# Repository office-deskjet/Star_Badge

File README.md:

## Star Badge
Inspired from Super Mario Brothers Super Star.  

### Features
5 SAO 1.69bis connectors, suporting I2C, X2 and X5 support GPIO.
Power by 2x AA batteries or USB micro
3.3 Volts, 1.5 Amps regulated

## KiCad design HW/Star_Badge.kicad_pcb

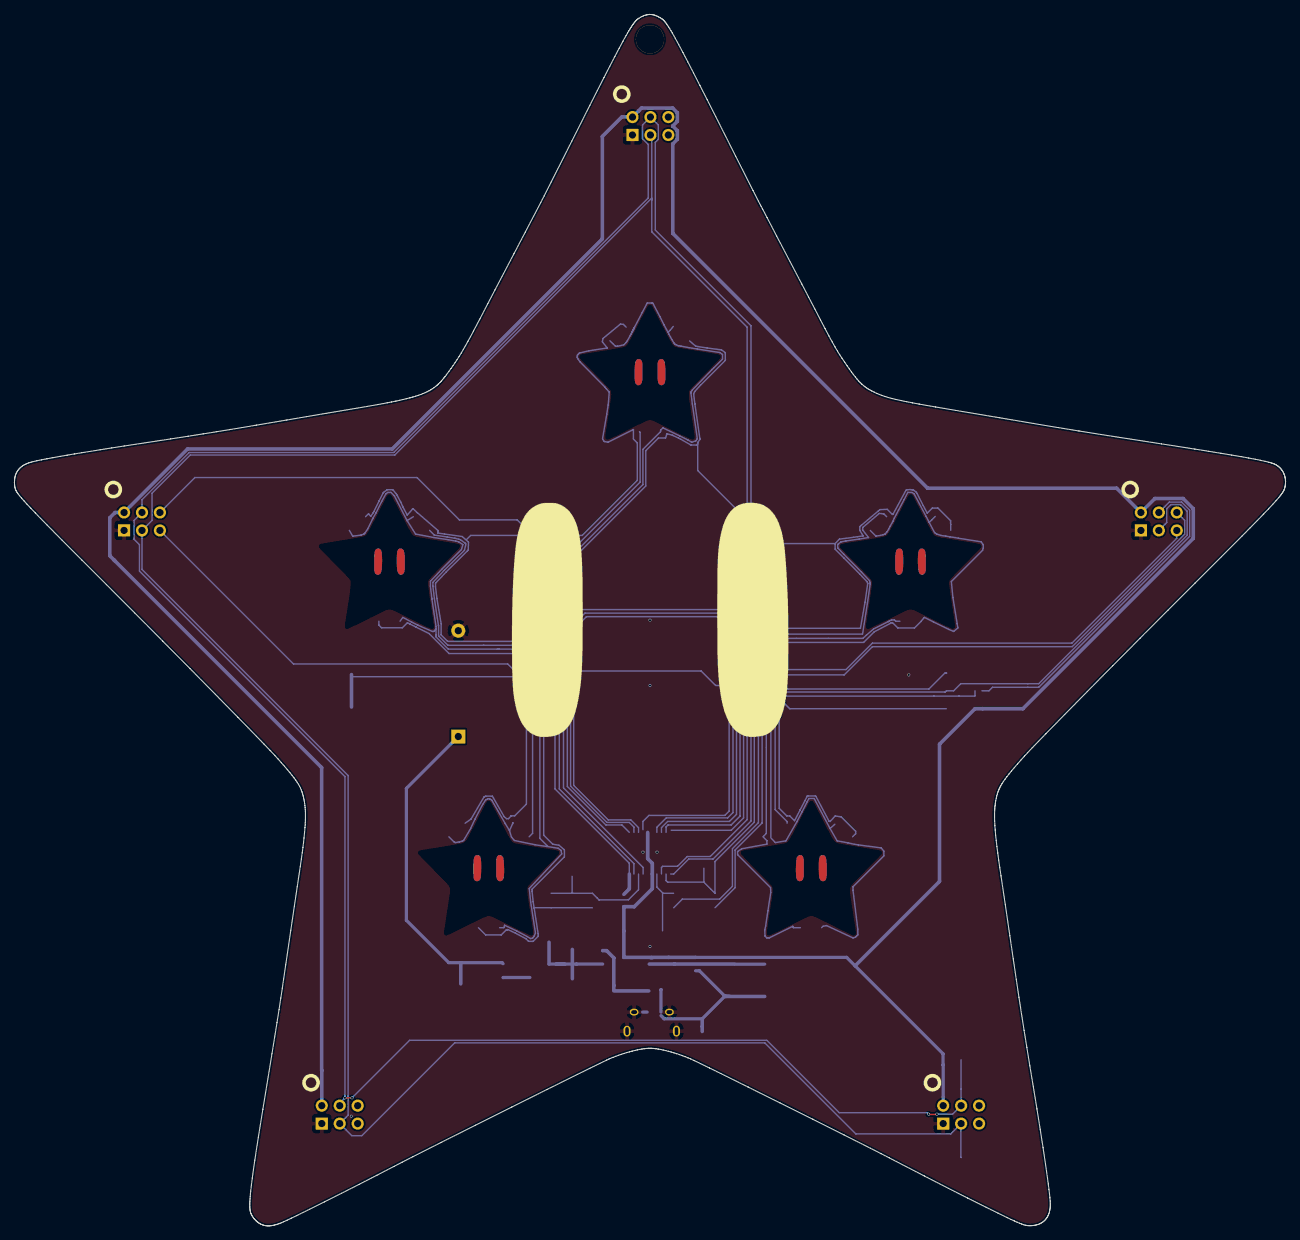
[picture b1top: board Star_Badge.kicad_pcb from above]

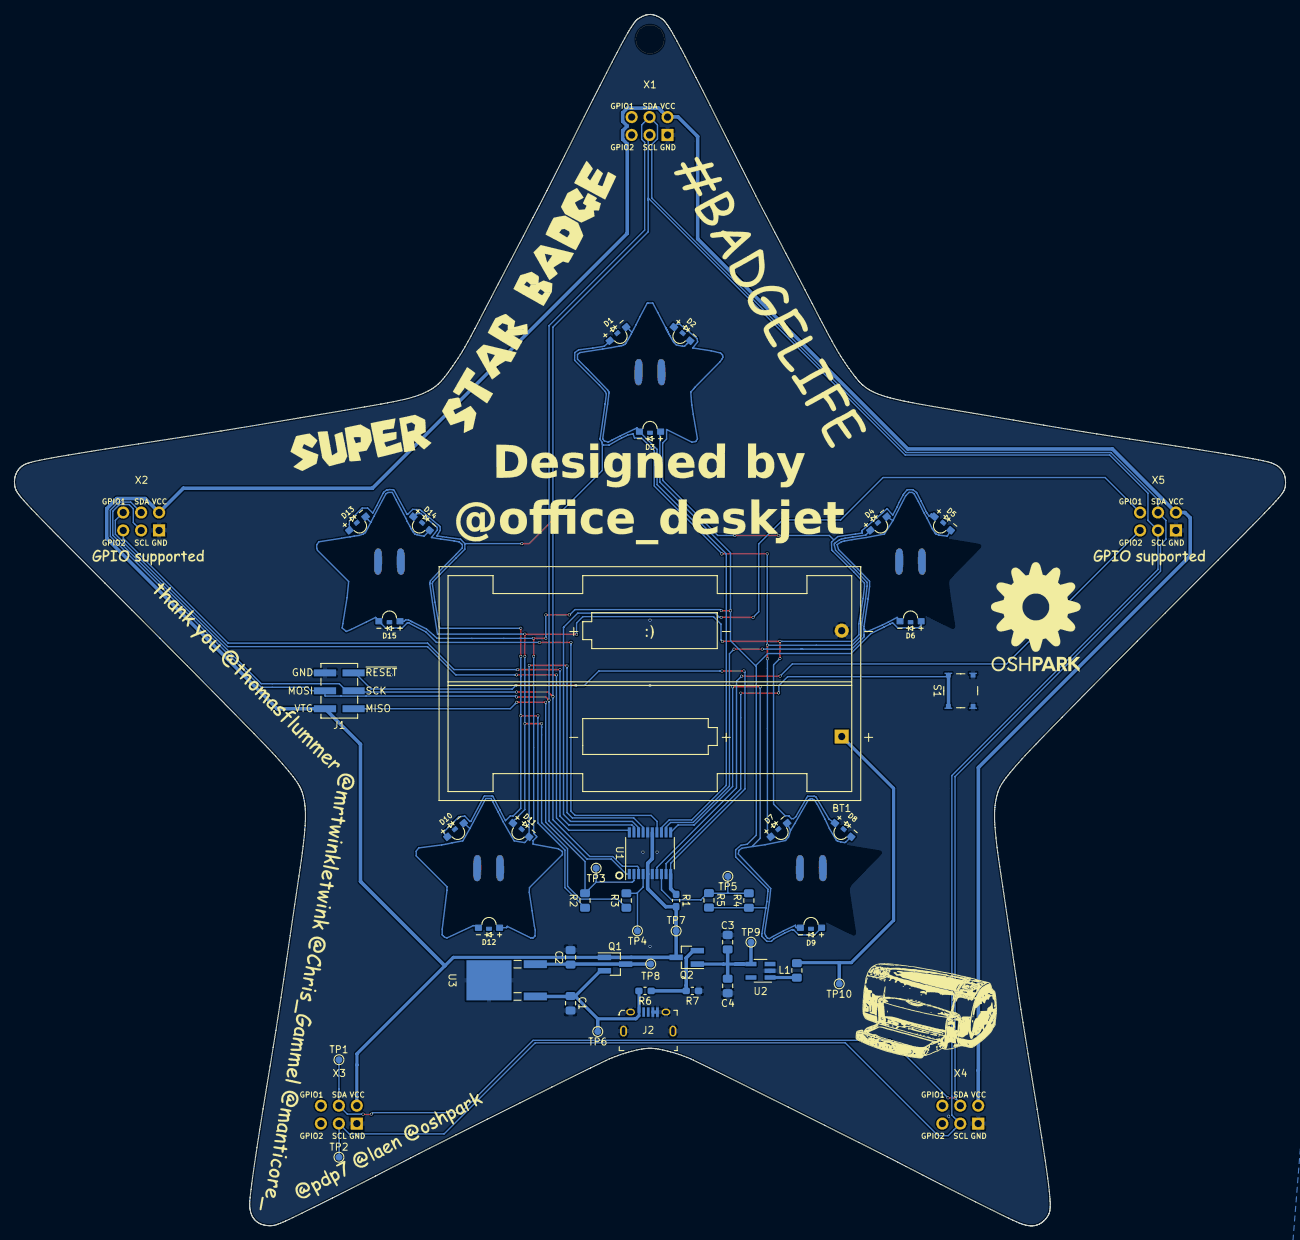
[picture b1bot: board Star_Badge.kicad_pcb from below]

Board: 2 copper layers, 180.0 x 171.6 mm, 51 parts (46 on the bottom side), 27 nets.

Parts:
BT1: Battery; BatteryHolder_Keystone_2462_2xAA
C1, C2, C3, C4: 10uF; C_0805_2012Metric_Pad1.15x1.40mm_HandSolder
D1, D4, D7, D10, D13: R_LED; 1204_SIDE_VIEW_LED
D2, D5, D8, D11, D14: G_LED; 1204_SIDE_VIEW_LED
D3, D6, D9, D12, D15: B_LED; 1204_SIDE_VIEW_LED
J1: AVR-ISP-6; AVR_ISP_2x3_P2.54mm_SMD
J2: 10118194-0001LF; USB_Micro_B_Female_10118194-0001LF
L1: 4.7uH; L_0805_2012Metric_Pad1.15x1.40mm_HandSolder
Q1: Q_NMOS_DGS; SOT-23_Handsoldering
Q2: Q_PMOS_DGS; SOT-23_Handsoldering
R1, R7: 6K8; R_0603_1608Metric_Pad1.05x0.95mm_HandSolder
R2, R4, R5: 50R; R_0805_2012Metric_Pad1.15x1.40mm_HandSolder
R3: 100R; R_0805_2012Metric_Pad1.15x1.40mm_HandSolder
R6: 4K7; R_0603_1608Metric_Pad1.05x0.95mm_HandSolder
S1: TL3315NF160Q; Switch_Tactile_SMD_4.5x4.5mm_TL3315NF160Q
TP1, TP2, TP3, TP4, TP5, TP6, TP7, TP8, TP9, TP10: TestPoint; TestPoint_Pad_D1.0mm
U1: ATTINY861-15XD; TSSOP-20_4.4x6.5mm_P0.65mm
U2: TPS613221ADBVT; SOT-23-5_HandSoldering
U3: AP7363-33D-13
X1, X2, X3, X4, X5: Badgelife_sao_connector_v169bis; Badgelife-SAOv169-BADGE-2x3

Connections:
/B_LED_BUS: D3.2, D6.2, D9.2, D12.2, D15.2, R4.1, R5.1
/B_PWM: R4.2, R5.2, TP5.1, U1.8
/Button: S1.1, S1.2, U1.9
/EN_RGB0: D10.1, D11.1, D12.1, U1.17
/EN_RGB1: D13.1, D14.1, D15.1, U1.14
/EN_RGB2: D1.1, D2.1, D3.1, U1.13
/EN_RGB3: D4.1, D5.1, D6.1, U1.12
/EN_RGB4: D7.1, D8.1, D9.1, U1.11
/GPIO_1_1: U1.20, X2.5
/GPIO_1_2: U1.19, X2.6
/GPIO_2_1: U1.18, X5.5
/GPIO_2_2: U1.7, X5.6
/G_LED_BUS: D2.2, D5.2, D8.2, D11.2, D14.2, R3.1
/G_PWM: R3.2, TP4.1, U1.4
/R_LED_BUS: D1.2, D4.2, D7.2, D10.2, D13.2, R2.1
/R_PWM__MISO: J1.1, R2.2, TP3.1, U1.2
/SCL_SCK: J1.3, TP2.1, U1.3, X1.4, X2.4, X3.4, X4.4, X5.4
/SDA_MOSI: J1.4, TP1.1, U1.1, X1.3, X2.3, X3.3, X4.3, X5.3
/VBUS: J1.2, Q1.1, Q2.3, R1.2, TP7.1, U1.5, U1.15, X1.1, X2.1, X3.1, X4.1, X5.1
/V_BAT: C3.1, C4.1, Q2.1, TP9.1, U2.4
/V_REG: C2.1, Q1.3, TP8.1, U3.3
/V_USB: C1.1, J2.1, Q1.2, R6.2, TP6.1, U3.1
/~RESET: J1.5, R1.1, U1.10
GND: BT1.2, C1.2, C2.2, C3.2, C4.2, J1.6, J2.4, J2.5, J2.SH, R7.1, S1.3, S1.4, U1.6, U1.16, U2.2, U3.2, X1.2, X2.2, X3.2, X4.2, X5.2
unnamed: BT1.1, L1.1, TP10.1
unnamed: L1.2, U2.1
unnamed: Q2.2, R6.1, R7.2

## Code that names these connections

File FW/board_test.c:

// Tests the board's functionality by blinking each LED per star one at a time.

#define F_CPU 8000000UL
#include <avr/io.h>
#include <util/delay.h>
#include <stdint.h>

// pins to enable the RGB LEDs
// LEDS are common cathode, 0 enables, 1 disables
#define EN_RGB0 (1 << PA3)
#define EN_RGB1 (1 << PA4)
#define EN_RGB2 (1 << PA5)
#define EN_RGB3 (1 << PA6)
#define EN_RGB4 (1 << PA7)

// PWM output pins
#define R_PWM   (1 << PB1)
#define G_PWM   (1 << PB3)
#define B_PWM   (1 << PB5)

#define NUM_RGB_LEDs 5
#define NUM_COLORS 3

uint8_t en_rgb_led[NUM_RGB_LEDs] = {EN_RGB0, EN_RGB1, EN_RGB2, EN_RGB3, EN_RGB4};
uint8_t colors[NUM_COLORS] = {R_PWM, G_PWM, B_PWM};

void setup()
{
    // enable output
    DDRA = EN_RGB4 | EN_RGB3 | EN_RGB2 | EN_RGB1 | EN_RGB0;
    DDRB = B_PWM | G_PWM | R_PWM;

    // diable all LEDs
    PORTA &= EN_RGB4 & EN_RGB3 & EN_RGB2 & EN_RGB1;

    // enable all LEDS
    //PORTA |= EN_RGB4 | EN_RGB3 | EN_RGB2 | EN_RGB1;

    // RBG LEDs are common Anode, logic one on cathod turns them off
    PORTB |= R_PWM | G_PWM | B_PWM;

}

int main()
{
    uint8_t led;
    uint8_t color;

    setup();

    for (;;) {
        for (led = 0; led < NUM_RGB_LEDs; led++) {
            for (color = 0; color < NUM_COLORS; color++) {
                PORTA |= en_rgb_led[led];
                PORTB &= ~colors[color];
                _delay_ms(1000);
                PORTB |= colors[color];
                PORTA &= ~(en_rgb_led[led]);
            }
        }
    }

    return 0;
}

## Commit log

2019-07-21 Starting over :(
2019-07-21 Added SAO connectors
2019-07-21 Added button. Moved parts around
2019-07-21 Added boost converter
2019-07-21 Added USB voltage regulator
2019-07-21 Added power circuits
2019-07-21 Added footprints
2019-07-21 Added netlist
2019-07-21 fixed footprints for U2 U3. Added 3D model to SOA connector
2019-07-21 Vreg 3D model, updated netlist
2019-07-21 fixing 3D models
2019-07-21 Removed paste from programming header, Fixed 3D model for Vreg?
2019-07-21 Removed through for battery holder. Will not be screwing it to PCB.
2019-07-21 Updated footprints: U2, U3. 3D models, U2, X1-5
2019-07-21 Base state image
2019-07-21 Add README.md
2019-07-22 layout of parts
2019-07-22 copper edge cuts
2019-07-22 B.Cu shows up in KiCad now.
2019-07-22 layers
2019-07-23 Added footprints for Copper, Silk, Mask layers
2019-07-23 Placed Battery holder
2019-07-23 Moved circle, outline to fab, SAO Connector
2019-07-23 trying to place SAO headers
2019-07-23 playing sao headers
2019-07-23 header locations are good
2019-07-23 adding keepouts to small stars
2019-07-23 4 stars now have keep out
2019-07-23 finished with star keepouts, moving around parts
2019-07-24 Roughly placed LEDs
2019-07-24 set trace and via settings. Set LED rotation
2019-07-24 Placed Blue LEDs
2019-07-24 LEDs placed
2019-07-24 Moved GPIO pinouts to X2 X3. New netlist, placing boost
2019-07-24 moved GPIO to X5. finished boost
2019-07-24 placed Vreg
2019-07-24 placed and routed power circuit. Power bus not routed.
2019-07-24 put back the drill hole that disapeared
2019-07-24 Added test points to schematic, new netlist
2019-07-24 Added test points to layout. Not placeed correctly yet
2019-07-24 added test point to batter pack output.
2019-07-24 Places power test points
2019-07-24 powered MCU, fixe U2 silk, connected RESET resistor
2019-07-24 Moved Switch, and PWM resistors - not finial moved test points to before resistors. - no new net
2019-07-24 update layout with new test points
2019-07-24 Spaced out parts
2019-07-24 Routing - net around star 3. Adjusted R G LED to route.
2019-07-24 Star 4 - net routing
2019-07-24 Adjusted the Y on the remaining LEDs
2019-07-24 Routed - net Star 5
2019-07-24 Routed - net Star 1
2019-07-24 Routed - net Star 2
2019-07-24 place RGB resistors and test points. not sure if best location.
2019-07-24 routed RGB around star 1
2019-07-24 routed RGB around star 2
2019-07-24 asd;kjas
2019-07-25 removed VBUS traces from top
2019-07-25 routed singles around start 5
2019-07-25 routed singles around start 1 and 2
2019-07-25 added power traces, may need to change
2019-07-25 Star 4 routing
2019-07-25 deleted power routign to get ground pour.
2019-07-25 moved button, Previous commit had i2c routign
2019-07-25 changed the enable pins for better routing and labled the associated star.
2019-07-25 spaced out the traces on Stars 3 and 4. Connect button
2019-07-25 star 5 wired
2019-07-25 43 unrouted singlas
2019-07-25 Star 2 and 3 routing
2019-07-25 routed miso mosi to programming header
2019-07-25 routed sclock to programming header
2019-07-25 routed gpio pins to SOA 2
2019-07-25 More routing
2019-07-25 G_LED_BUS connected
2019-07-25 R_LED_BUS connected
2019-07-25 fixed issue with soldermask being pulled around eyes silk
2019-07-25 RESET wrired
2019-07-25 x1 fully connected, changed group pour setting on bottom copper
2019-07-25 hide traces under headers
2019-07-25 SDA SCL wired to headers
2019-07-25 fixed button traces
2019-07-25 added gnd vias, layout done
2019-07-25 removed ground pour from front and back of art
2019-07-25 updated B and F Cu art
2019-07-25 working on silk art
2019-07-25 wokring on thank you art
2019-07-26 finsihed art work. AVR HEADER BAD??
2019-07-26 Finished back silk art:
2019-07-26 clean up lettering b silk
2019-07-26 clean up lettering more
2019-07-26 fixed mask setting
2019-07-26 adding gerbers
2019-07-29 Changed art for fab with OSH Park
2019-08-04 OSH Park gerber files. FW test code in development
2019-08-04 added pin definitions

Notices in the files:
parts and their libraries:
Copyright 2016 Accelerated Designs. All rights reserved.
